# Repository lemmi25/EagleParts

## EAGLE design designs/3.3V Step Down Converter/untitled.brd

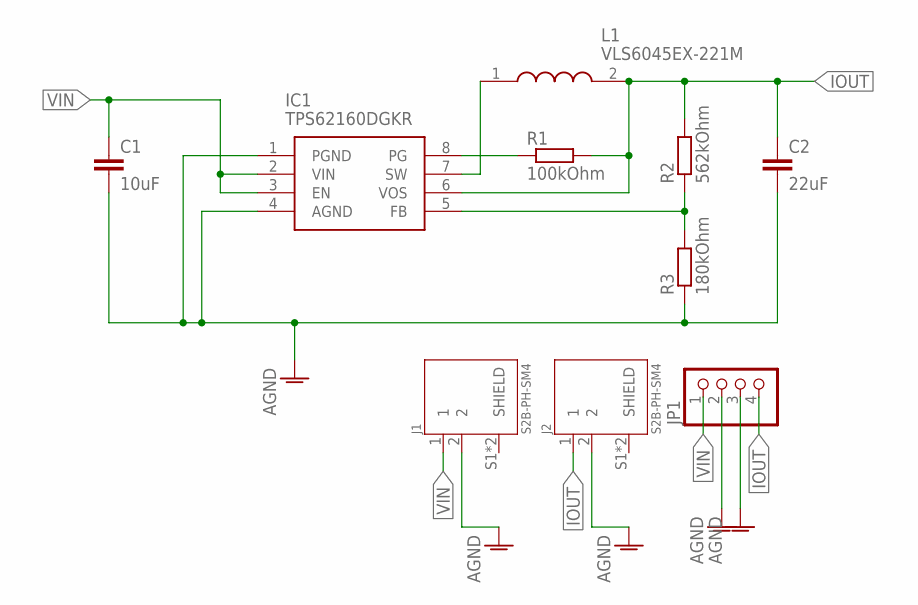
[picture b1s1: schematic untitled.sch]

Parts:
C1: 10uF; C1206
C2: 22uF; C0805K
IC1: TPS62160DGKR; SOP65P490X110-8N
J1, J2: S2B-PH-SM4; JST_S2B-PH-SM4-TB(LF)(SN)
JP1: PINHD-1X4; 1X04
L1: VLS6045EX-221M; INDPM6060X450N
R1: 100kOhm; R1206
R2: 562kOhm; R0805
R3: 180kOhm; R0402

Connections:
AGND: C1.2, C2.2, IC1.1 (PGND), IC1.4 (AGND), J1.2, J2.2, JP1.2, JP1.3, R3.1
FB2: IC1.5 (FB), R2.1, R3.2
IOUT: C2.1, IC1.6 (VOS), J2.1, JP1.4, L1.2, R1.2, R2.2
PG2: IC1.8 (PG), R1.1
SW2: IC1.7 (SW), L1.1
VIN: C1.1, IC1.2 (VIN), IC1.3 (EN), J1.1, JP1.1

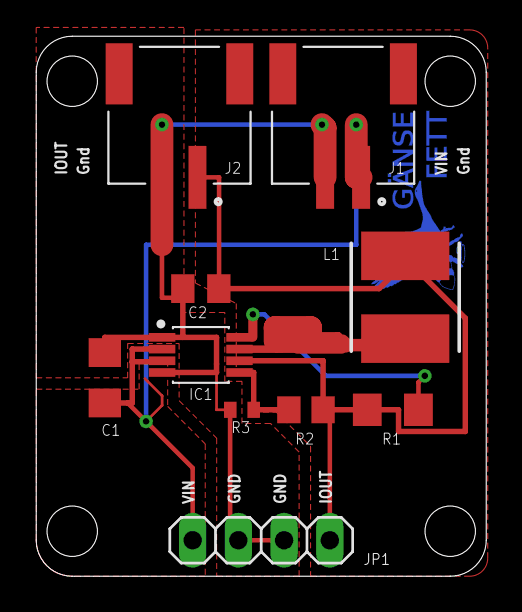
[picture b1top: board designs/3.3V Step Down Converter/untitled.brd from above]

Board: 2 copper layers, 25.0 x 30.0 mm, 10 parts (0 on the bottom side), 6 nets.

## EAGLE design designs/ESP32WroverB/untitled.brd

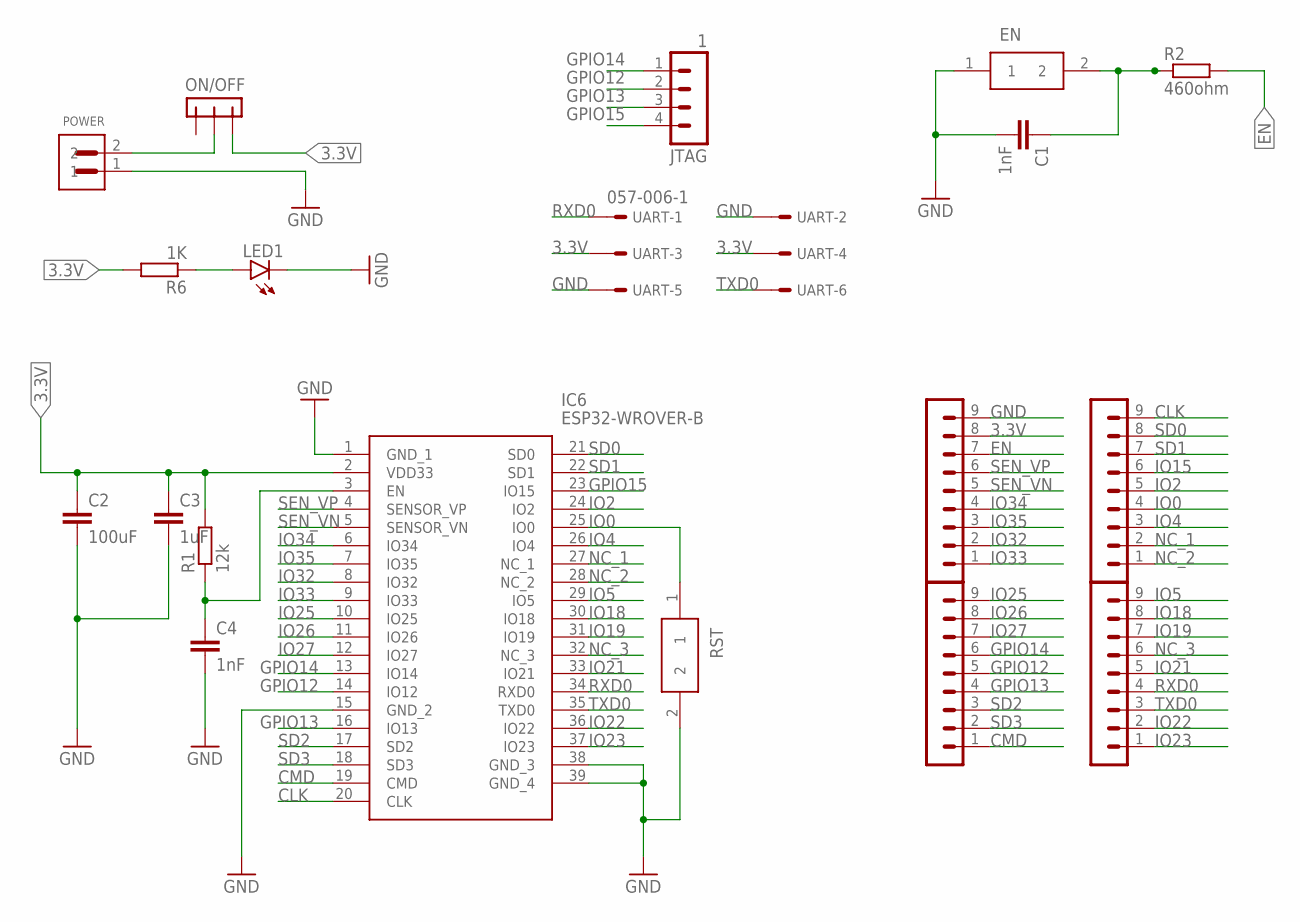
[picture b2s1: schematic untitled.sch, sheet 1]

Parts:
C1, C4: 1nF; C0805
C2: 100uF; C1206
C3: 1uF; C0805
EN: FSMSMTR; FSMSM
IC6: ESP32-WROVER-B; ESP32WROVERIB16MB
JTAG: 1; MA04-1
LED1: LEDSMT1206; 1206
ON/OFF: -CON3; CON3
POWER: S2B-PH-SM4-TB; JST_S2B-PH-SM4-TB
R1: 12k; R0805
R2: 460ohm; R0805
R6: 1K; R1206
RST: FSMSMTR; FSMSM
SV1, SV2, SV5, SV6: PINHEADER-1X9; MA09-1
UART: 057-006-1

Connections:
3.3V: C2.1, C3.1, IC6.2 (VDD33), ON/OFF.P$1 (1), R1.2, R6.2, SV5.8, UART.3, UART.4
CLK: IC6.20 (CLK), SV1.9
CMD: IC6.19 (CMD), SV6.1
EN: C1.1, C4.1, EN.2, IC6.3 (EN), R1.1, R2.1, R2.2, SV5.7
GND: C1.2, C2.2, C3.2, C4.2, EN.1, IC6.1 (GND_1), IC6.15 (GND_2), IC6.38 (GND_3), IC6.39 (GND_4), LED1.C, POWER.1, RST.2, SV5.9, UART.2, UART.5
GPIO12: IC6.14 (IO12), JTAG.2, SV6.5
GPIO13: IC6.16 (IO13), JTAG.3, SV6.4
GPIO14: IC6.13 (IO14), JTAG.1, SV6.6
IO0: IC6.25 (IO0), RST.1, SV1.4
IO2: IC6.24 (IO2), SV1.5
IO4: IC6.26 (IO4), SV1.3
IO5: IC6.29 (IO5), SV2.9
IO18: IC6.30 (IO18), SV2.8
IO19: IC6.31 (IO19), SV2.7
IO21: IC6.33 (IO21), SV2.5
IO22: IC6.36 (IO22), SV2.2
IO23: IC6.37 (IO23), SV2.1
IO25: IC6.10 (IO25), SV6.9
IO26: IC6.11 (IO26), SV6.8
IO27: IC6.12 (IO27), SV6.7
IO32: IC6.8 (IO32), SV5.2
IO33: IC6.9 (IO33), SV5.1
IO34: IC6.6 (IO34), SV5.4
IO35: IC6.7 (IO35), SV5.3
unnamed: ON/OFF.P$2 (2), POWER.2
unnamed: LED1.A, R6.1
NC_1: IC6.27 (NC_1), SV1.2
NC_2: IC6.28 (NC_2), SV1.1
NC_3: IC6.32 (NC_3), SV2.6
RXD0: IC6.34 (RXD0), SV2.4, UART.1
SD0: IC6.21 (SD0), SV1.8
SD1: IC6.22 (SD1), SV1.7
SD2: IC6.17 (SD2), SV6.3
SD3: IC6.18 (SD3), SV6.2
SEN_VN: IC6.5 (SENSOR_VN), SV5.5
SEN_VP: IC6.4 (SENSOR_VP), SV5.6
TXD0: IC6.35 (TXD0), SV2.3, UART.6

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
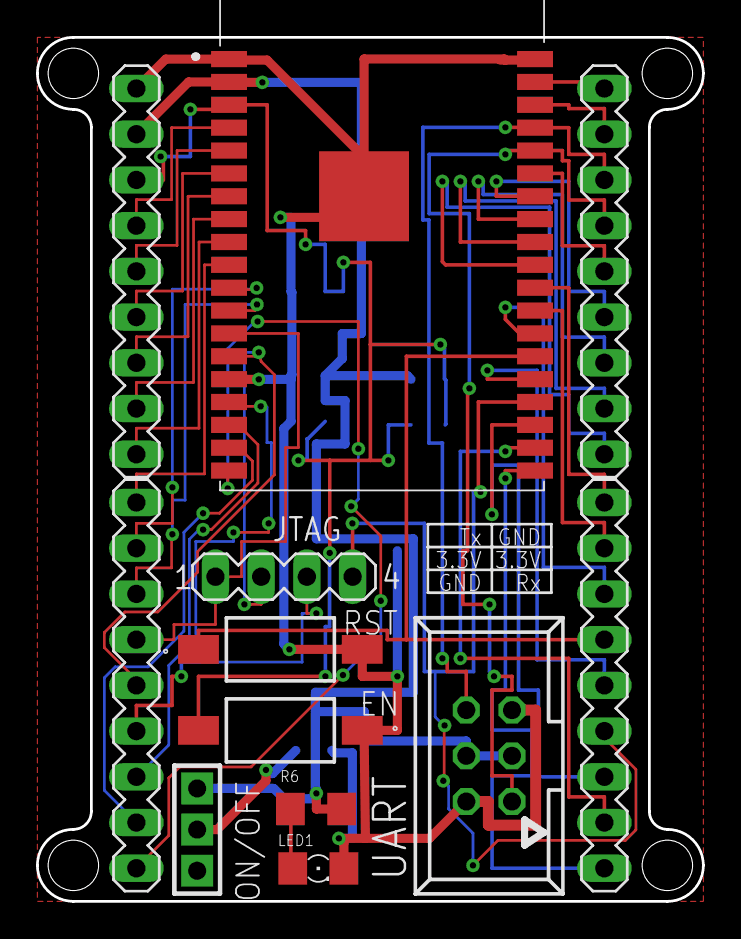
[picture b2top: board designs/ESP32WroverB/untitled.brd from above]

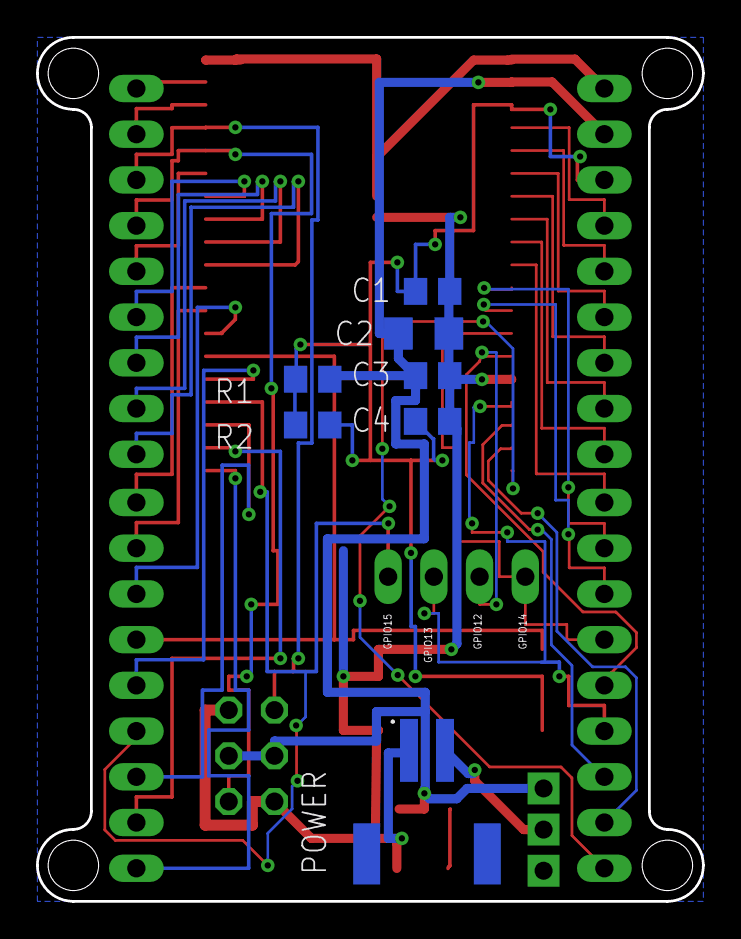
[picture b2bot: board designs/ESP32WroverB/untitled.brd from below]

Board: 2 copper layers, 37.0 x 48.0 mm, 19 parts (7 on the bottom side), 38 nets.

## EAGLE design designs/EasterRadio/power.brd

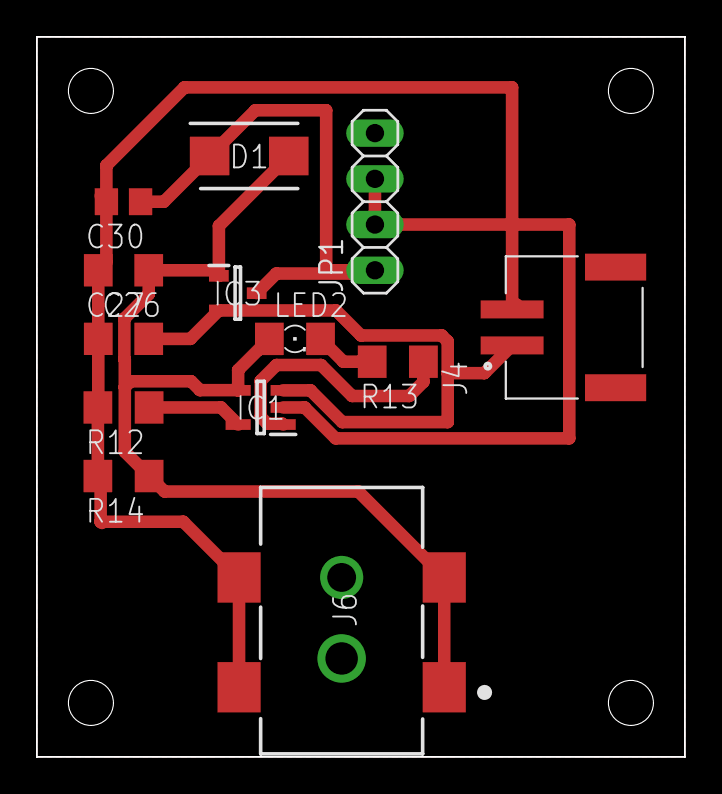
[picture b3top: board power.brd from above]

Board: 2 copper layers, 36.0 x 40.0 mm, 13 parts (0 on the bottom side), 7 nets.

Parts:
C26, C27: 4.7uF; C1206
C30: 1uF; C0805
D1: LSM115JE3_TR13; DIOM5436X330N
IC1: MCP73832T-2ACI_OT; SOT95P270X145-5N
IC3: DMP1045U-7; SOT96P240X100-3N
J4: S2B-PH-SM4; JST_S2B-PH-SM4-TB(LF)(SN)
J6: PJ-002AH-SMT-TR
JP1: 1X04
LED2: 1206
R12: 0; R1206
R13: 470ohm; R1206
R14: 100K; R1206

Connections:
5V: C27.1, D1.2, IC1.4, IC3.1, J6.1, J6.2, LED2.A, R14.1
GNDA: C26.1, C27.2, C30.2, IC1.2, J4.2, J6.3, J6.4, JP1.2, JP1.3, R12.2, R14.2
unnamed: LED2.C, R13.2
PROG: IC1.5, R12.1
STAT: IC1.1, R13.1
U_DRAIN: C30.1, D1.1, IC3.3, JP1.1
VBAT: C26.2, IC1.3, IC3.2, J4.1

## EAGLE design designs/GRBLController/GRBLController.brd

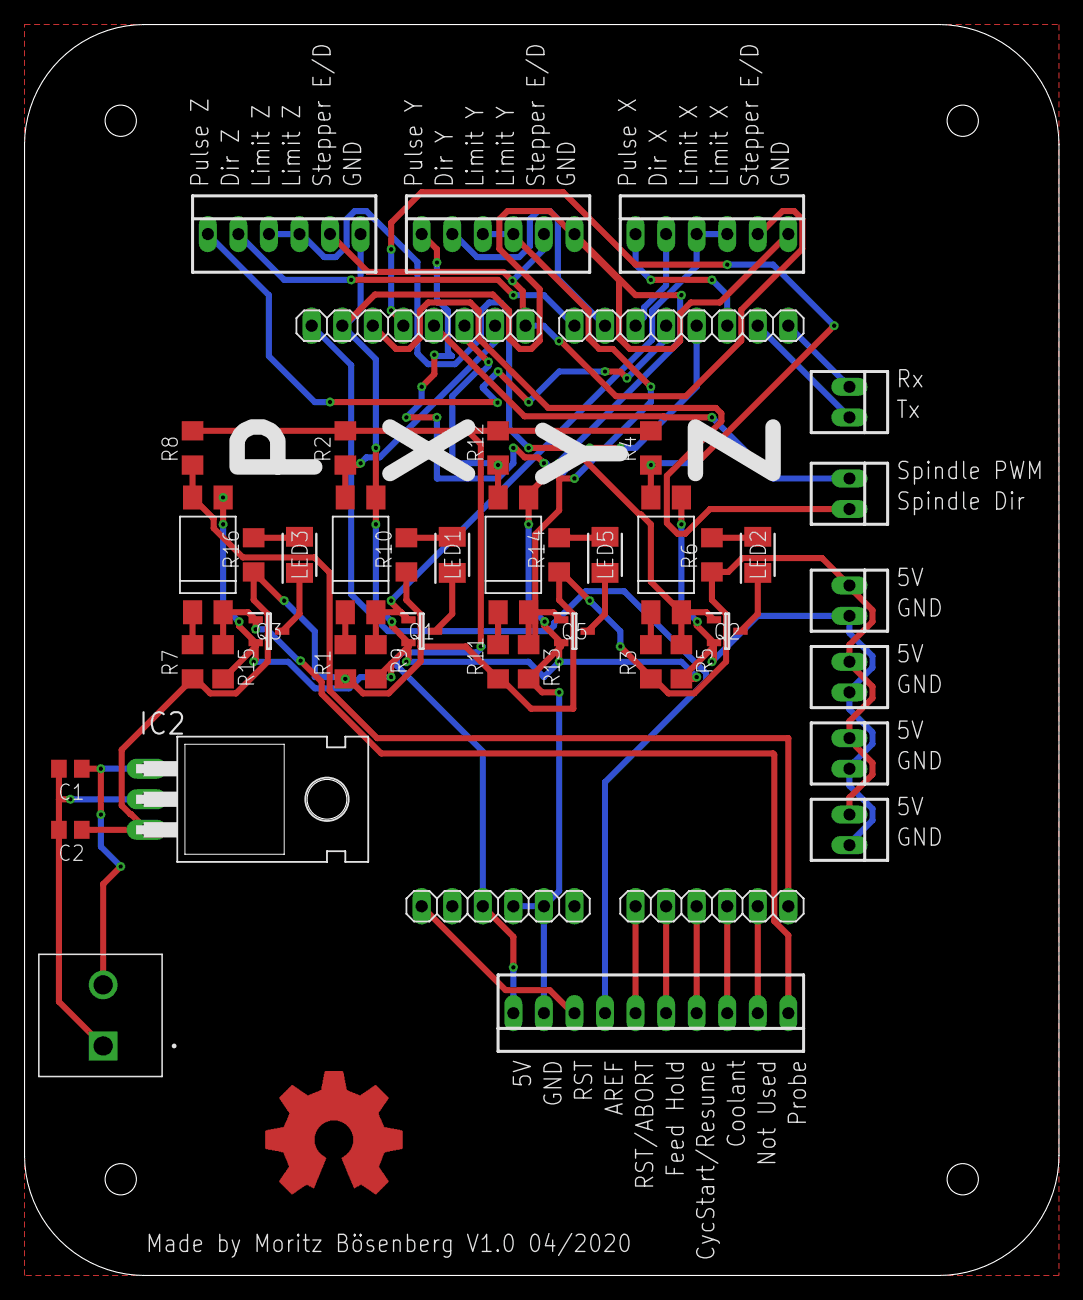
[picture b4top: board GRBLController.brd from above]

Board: 2 copper layers, 86.0 x 104.0 mm, 43 parts (0 on the bottom side), 43 nets.

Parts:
C1: 470nF; C0805
C2: 100nF; C0805
IC1: ARDUINO2009_2
IC2: 7805T; TO220H
J1: SCREW_PITCH_508; CUI_TB007-508-02BE
LED1, LED2, LED3, LED5: PLCC2; LEDM3528X200N
OK1, OK2, OK3, OK5: LTVOPTOS; DIL4-SMD
Q1, Q2, Q3, Q5: FDN5632N-F085; SOT95P237X122-3N
R1, R3, R7, R11: 220; R1206
R2, R4, R8, R12: 1K; R1206
R5, R6, R9, R10, R13, R14, R15, R16: 10K; R1206
X1, X2, X4, X8, X9, X10: 22-23-2021
X3: 22-23-2101
X5, X6, X7: 22-23-2061

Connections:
5V_ARDUINO: IC1.3, R2.2, R4.2, R8.2, R12.2, X3.10
5V_O: C2.1, IC2.3, R1.1, R3.1, R6.1, R7.1, R10.1, R11.1, R14.1, R16.1, X4.1, X8.1, X9.1, X10.1
24V: C1.1, IC2.1, J1.2
!RESET: IC1.1, X3.8
AGND: IC1.4, IC1.5, IC1.27, OK1.3, OK2.3, OK3.3, OK5.3, Q1.2, Q2.2, Q3.2, Q5.2, R5.2, R9.2, R13.2, R15.2, X3.9, X4.2, X5.6, X6.6, X7.6, X8.2, X9.2, X10.2
AREF: IC1.28, X3.7
COOLANT: IC1.10, X3.3
CYCLE_START/RESUME: IC1.9, X3.4
DIRECTION_X: IC1.18, X5.2
DIRECTION_Y: IC1.19, X6.2
DIRECTION_Z: IC1.20, X7.2
FEED_HOLD: IC1.8, X3.5
LIMIT_X: IC1.22, OK1.4, R2.1
LIMIT_X_SCREW: OK1.2, Q1.1, R9.1, X5.3, X5.4
LIMIT_Y: IC1.23, OK5.4, R12.1
LIMIT_Y_SCREW: OK5.2, Q5.1, R13.1, X6.3, X6.4
LIMIT_Z: IC1.25, OK2.4, R4.1
LIMIT_Z_SCREW: OK2.2, Q2.1, R5.1, X7.3, X7.4
unnamed: OK1.1, R1.2
unnamed: LED1.2, R10.2
unnamed: LED1.1, Q1.3
unnamed: OK5.1, R11.2
unnamed: LED5.2, R14.2
unnamed: LED5.1, Q5.3
unnamed: OK2.1, R3.2
unnamed: LED2.2, R6.2
unnamed: LED2.1, Q2.3
unnamed: OK3.1, R7.2
unnamed: LED3.2, R16.2
unnamed: LED3.1, Q3.3
unnamed: C1.2, C2.2, IC2.2, J1.1
NOT_USED: IC1.11, X3.2
PROBE: IC1.12, OK3.4, R8.1
PROBE_SCREW: OK3.2, Q3.1, R15.1, X3.1
PULSE_X: IC1.15, X5.1
PULSE_Y: IC1.16, X6.1
PULSE_Z: IC1.17, X7.1
RESET/ABORT: IC1.7, X3.6
RX: IC1.13, X1.1
SPINDLE_DIRECTION: IC1.26, X2.2
SPINDLE_PWM: IC1.24, X2.1
STEPPER_ENABLE/DISABLE: IC1.21, X5.5, X6.5, X7.5
TX: IC1.14, X1.2

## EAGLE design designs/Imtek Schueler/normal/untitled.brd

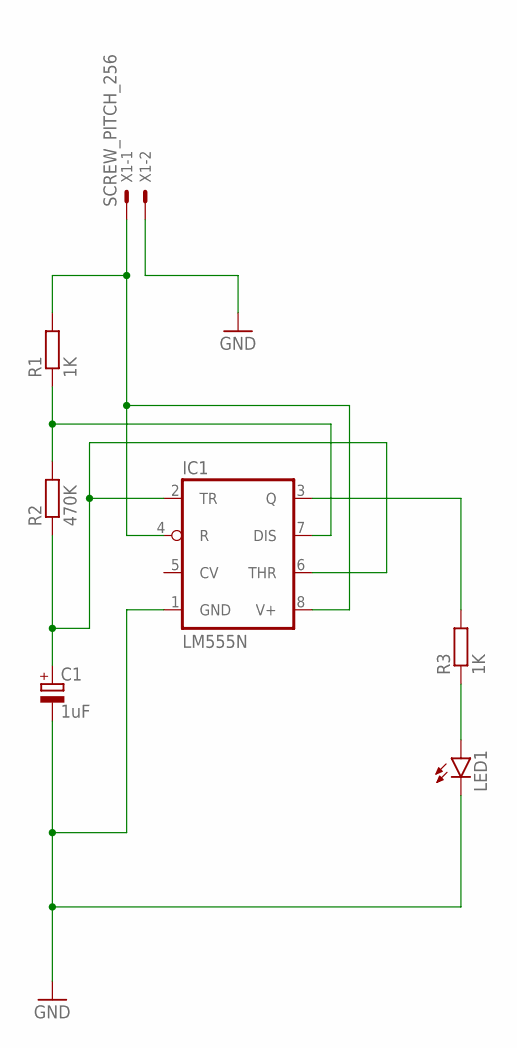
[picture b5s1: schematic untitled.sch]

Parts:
C1: 1uF; E2-5
IC1: LM555N; DIL08
LED1: LED_1206SMT1206; 1206
R1, R3: 1K; 0207/10
R2: 470K; 0207/10
X1: SCREW_PITCH_256; 22-23-2021

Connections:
GND: C1.-, IC1.1 (GND), LED1.C, X1.2
unnamed: C1.+, IC1.2 (TR), IC1.6 (THR), R2.1
unnamed: LED1.A, R3.1
unnamed: IC1.7 (DIS), R1.1, R2.2
unnamed: IC1.4 (R), IC1.8 (V+), R1.2, X1.1
unnamed: IC1.3 (Q), R3.2

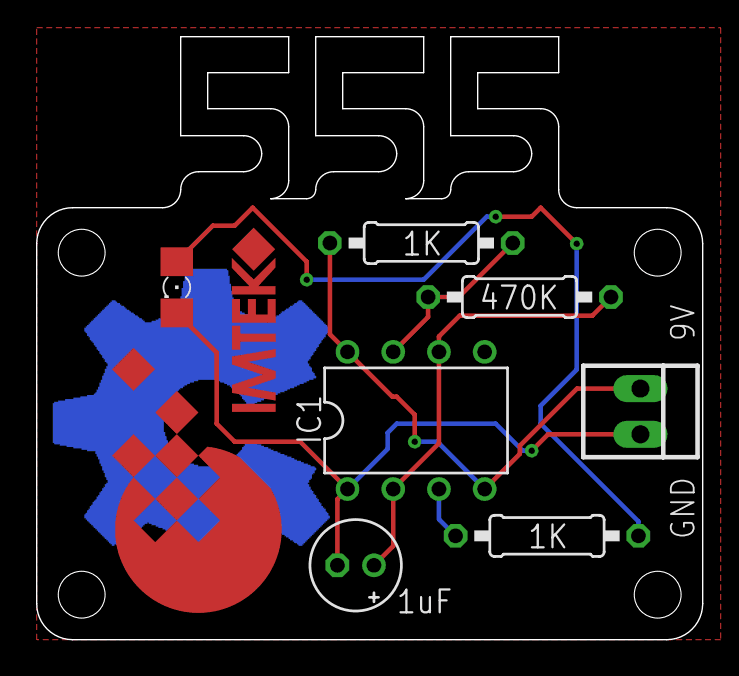
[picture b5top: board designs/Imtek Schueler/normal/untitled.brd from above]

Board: 2 copper layers, 37.0 x 33.5 mm, 7 parts (0 on the bottom side), 6 nets.

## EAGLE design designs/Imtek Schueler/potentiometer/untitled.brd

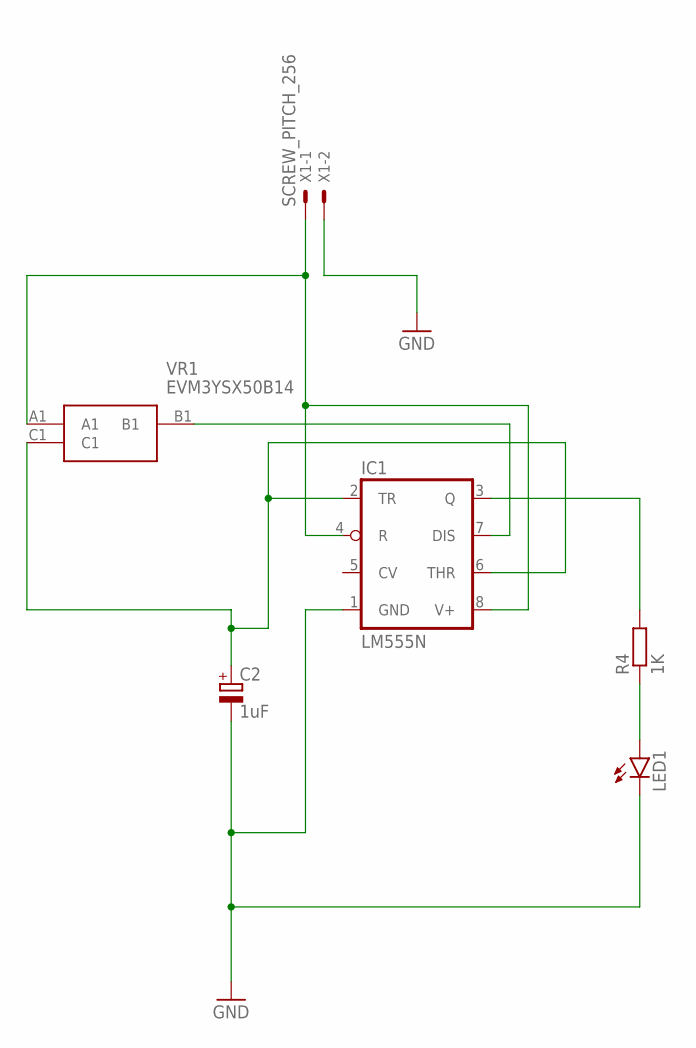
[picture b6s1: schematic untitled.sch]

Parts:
C2: 1uF; E2-5
IC1: LM555N; DIL08
LED1: LED_1206SMT1206; 1206
R4: 1K; 0207/10
VR1: EVM3YSX50B14
X1: SCREW_PITCH_256; 22-23-2021

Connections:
GND: C2.-, IC1.1 (GND), LED1.C, X1.2
unnamed: C2.+, IC1.2 (TR), IC1.6 (THR), VR1.C1
unnamed: LED1.A, R4.1
unnamed: IC1.7 (DIS), VR1.B1
unnamed: IC1.4 (R), IC1.8 (V+), VR1.A1, X1.1
unnamed: IC1.3 (Q), R4.2

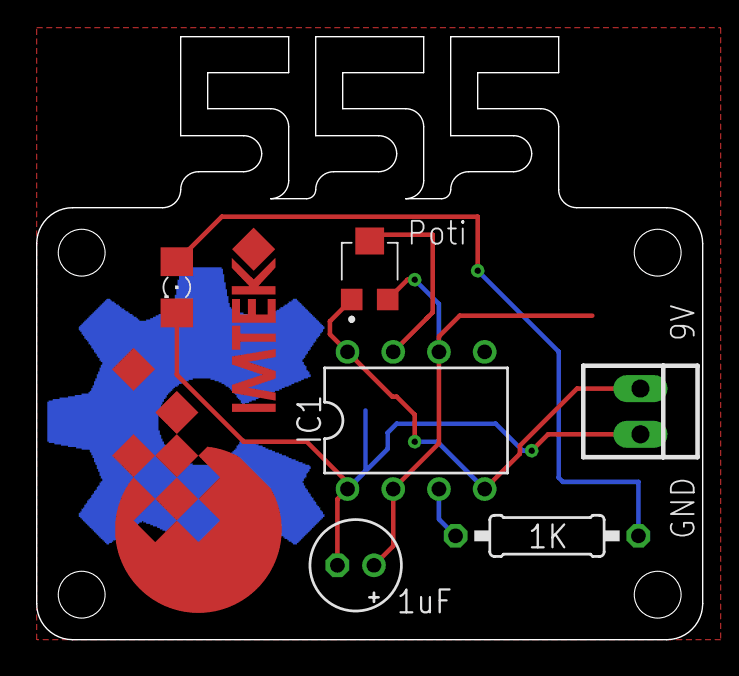
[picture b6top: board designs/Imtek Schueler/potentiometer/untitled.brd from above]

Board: 2 copper layers, 37.0 x 33.5 mm, 6 parts (0 on the bottom side), 6 nets.

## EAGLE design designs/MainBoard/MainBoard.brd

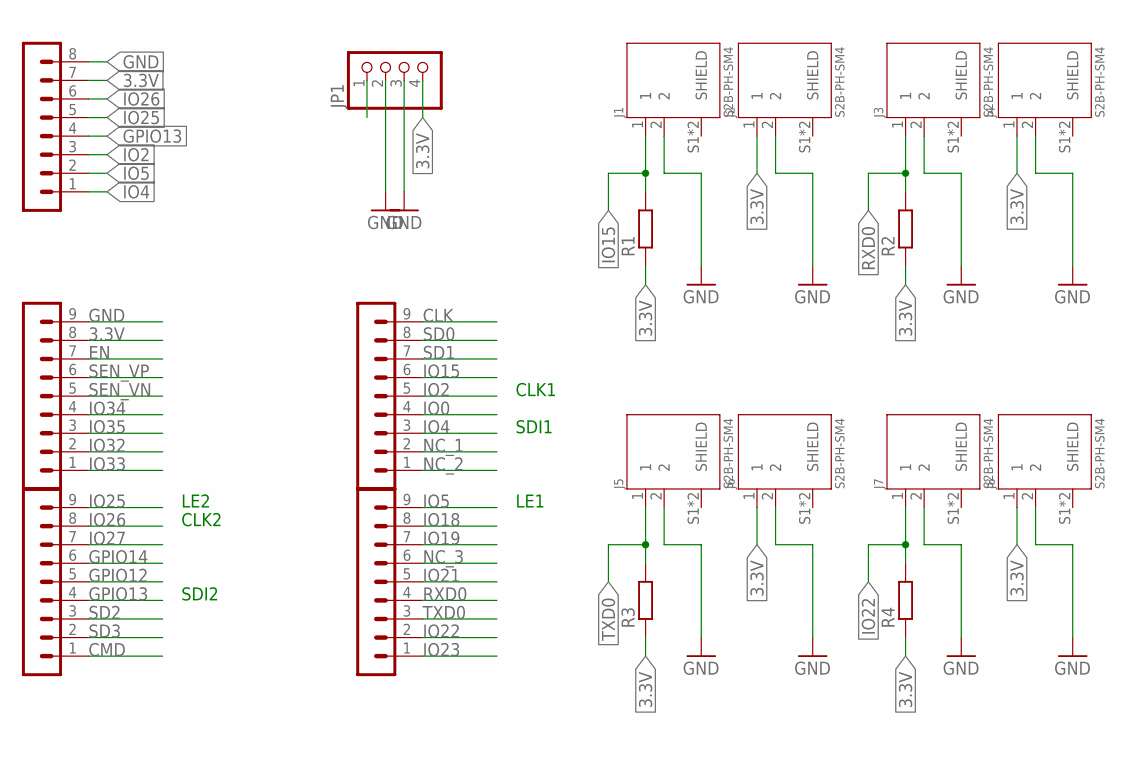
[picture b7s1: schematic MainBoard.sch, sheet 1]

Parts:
J1, J2, J3, J4, J5, J6, J7, J8: S2B-PH-SM4; JST_S2B-PH-SM4-TB(LF)(SN)
JP1: PINHD-1X4; 1X04
R1, R2, R3, R4: R-EU_1206R1206; R1206
SV2, SV3, SV5, SV6: PINHEADER-1X9; MA09-1
SV4: PINHEADER-1X8; MA08-1

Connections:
3.3V: J2.1, J4.1, J6.1, J8.1, JP1.4, R1.1, R2.1, R3.1, R4.1, SV4.7, SV5.8
CLK: SV2.9
CMD: SV6.1
EN: SV5.7
GND: J1.2, J2.2, J3.2, J4.2, J5.2, J6.2, J7.2, J8.2, JP1.2, JP1.3, SV4.8, SV5.9
GPIO12: SV6.5
GPIO13: SV4.4, SV6.4
GPIO14: SV6.6
IO0: SV2.4
IO2: SV2.5, SV4.3
IO4: SV2.3, SV4.1
IO5: SV3.9, SV4.2
IO15: J1.1, R1.2, SV2.6
IO18: SV3.8
IO19: SV3.7
IO21: SV3.5
IO22: J7.1, R4.2, SV3.2
IO23: SV3.1
IO25: SV4.5, SV6.9
IO26: SV4.6, SV6.8
IO27: SV6.7
IO32: SV5.2
IO33: SV5.1
IO34: SV5.4
IO35: SV5.3
NC: JP1.1
NC_1: SV2.2
NC_2: SV2.1
NC_3: SV3.6
RXD0: J3.1, R2.2, SV3.4
SD0: SV2.8
SD1: SV2.7
SD2: SV6.3
SD3: SV6.2
SEN_VN: SV5.5
SEN_VP: SV5.6
TXD0: J5.1, R3.2, SV3.3

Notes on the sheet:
CLK1
CLK2
LE1
LE2
SDI1
SDI2

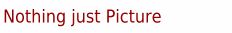
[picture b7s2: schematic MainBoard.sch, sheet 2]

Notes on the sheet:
Nothing just Picture

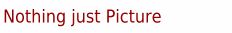
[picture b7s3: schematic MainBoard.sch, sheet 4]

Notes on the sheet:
Nothing just Picture

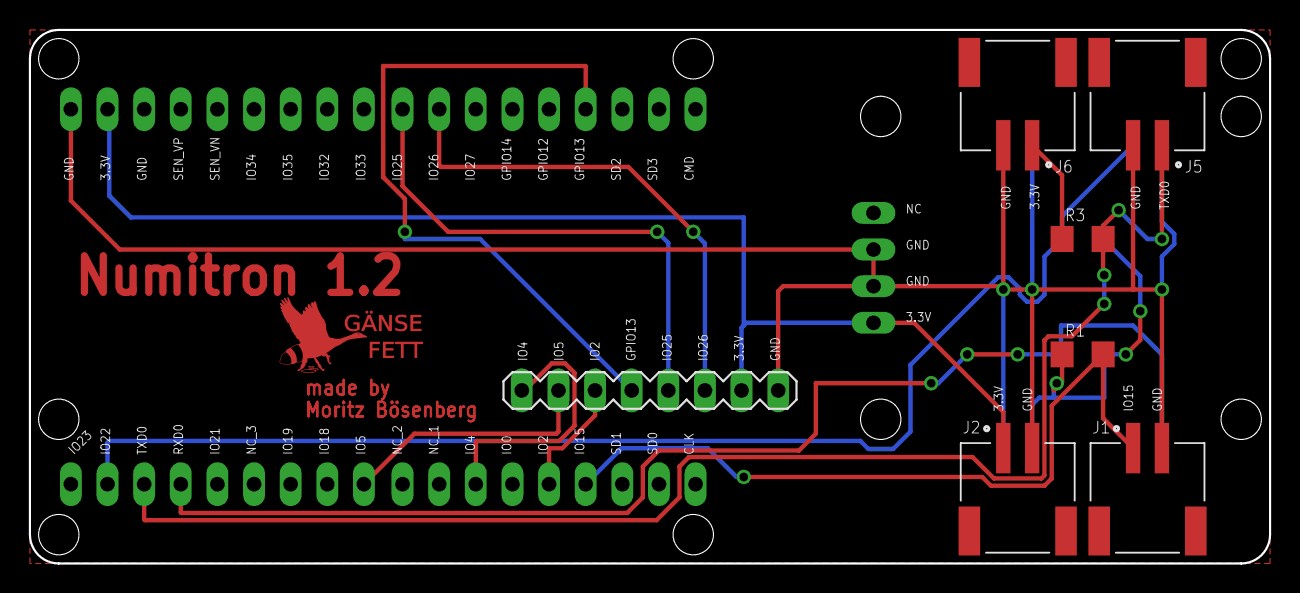
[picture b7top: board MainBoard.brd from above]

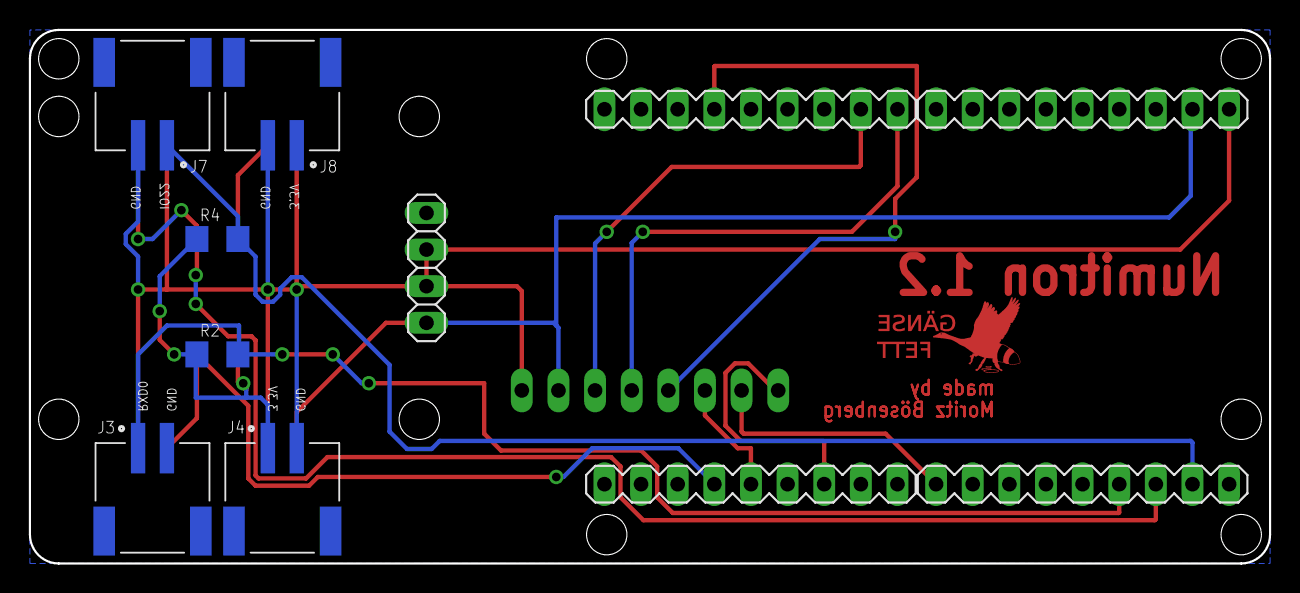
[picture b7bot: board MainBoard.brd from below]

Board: 2 copper layers, 86.0 x 37.0 mm, 18 parts (11 on the bottom side), 12 nets.

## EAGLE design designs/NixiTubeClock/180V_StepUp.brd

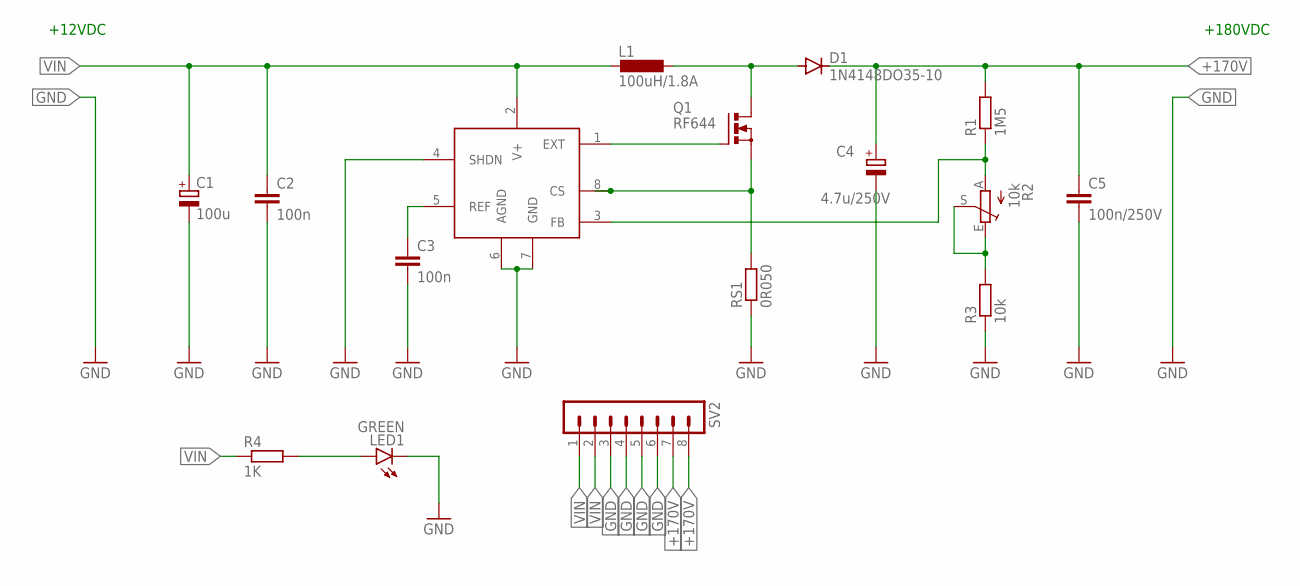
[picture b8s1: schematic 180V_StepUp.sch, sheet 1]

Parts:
C1: 100u; E2,5-7
C2, C3: 100n; C0805
C4: 4.7u/250V; E2,5-7
C5: 100n/250V; C2225K
D1: 1N4148DO35-10; DO35-10
IC1: MAX1771; SO08
L1: 100uH/1.8A; DO3316P
LED1: GREEN; 1206
Q1: RF644; TO220BV
R1: 1M5; R0805
R2: 10k; RJ9W
R3: 10k; R0805
R4: 1K; R1206
RS1: 0R050; 0207/10
SV2: MA08-1

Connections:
+170V: C4.+, C5.1, D1.C, R1.2, SV2.7, SV2.8
GND: C1.-, C2.2, C3.2, C4.-, C5.2, IC1.4 (SHDN), IC1.6 (AGND), IC1.7 (GND), LED1.C, R3.1, RS1.1, SV2.3, SV2.4, SV2.5, SV2.6
unnamed: LED1.A, R4.2
unnamed: D1.A, L1.2, Q1.D
unnamed: C3.1, IC1.5 (REF)
unnamed: IC1.1 (EXT), Q1.G
unnamed: IC1.8 (CS), Q1.S, RS1.2
unnamed: IC1.3 (FB), R1.1, R2.A
unnamed: R2.E, R2.S, R3.2
VIN: C1.+, C2.1, IC1.2 (V+), L1.1, R4.1, SV2.1, SV2.2

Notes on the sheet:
+12VDC
+180VDC

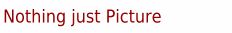
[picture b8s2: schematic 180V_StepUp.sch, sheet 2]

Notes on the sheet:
Nothing just Picture

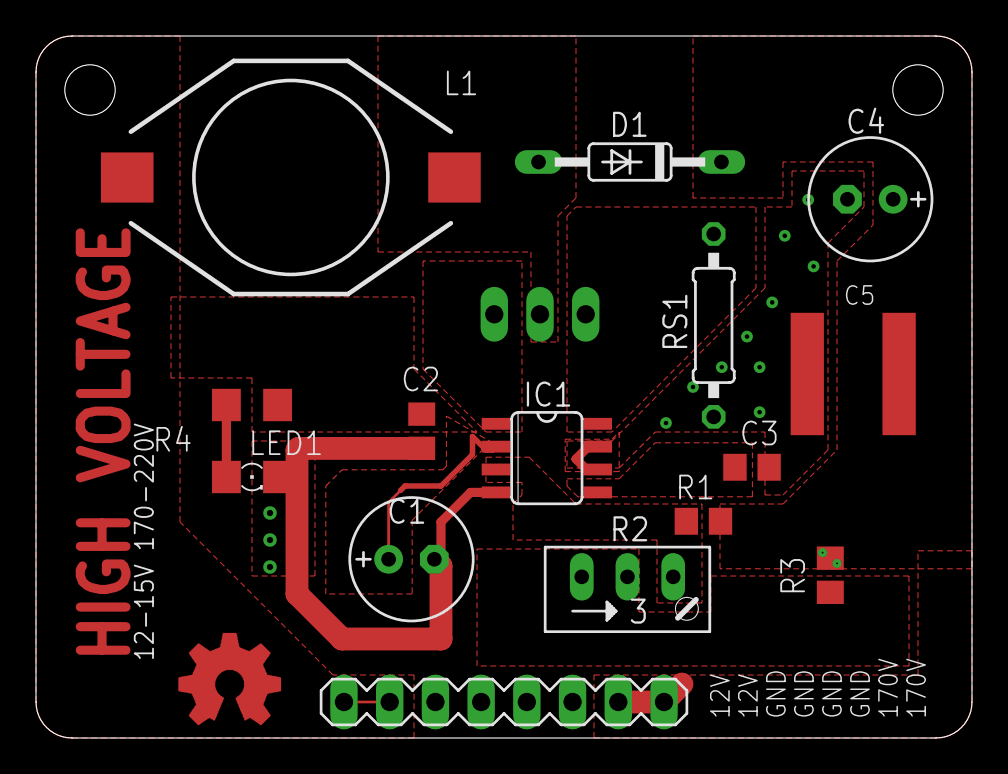
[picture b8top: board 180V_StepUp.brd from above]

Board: 2 copper layers, 52.0 x 39.0 mm, 16 parts (1 on the bottom side), 10 nets.
